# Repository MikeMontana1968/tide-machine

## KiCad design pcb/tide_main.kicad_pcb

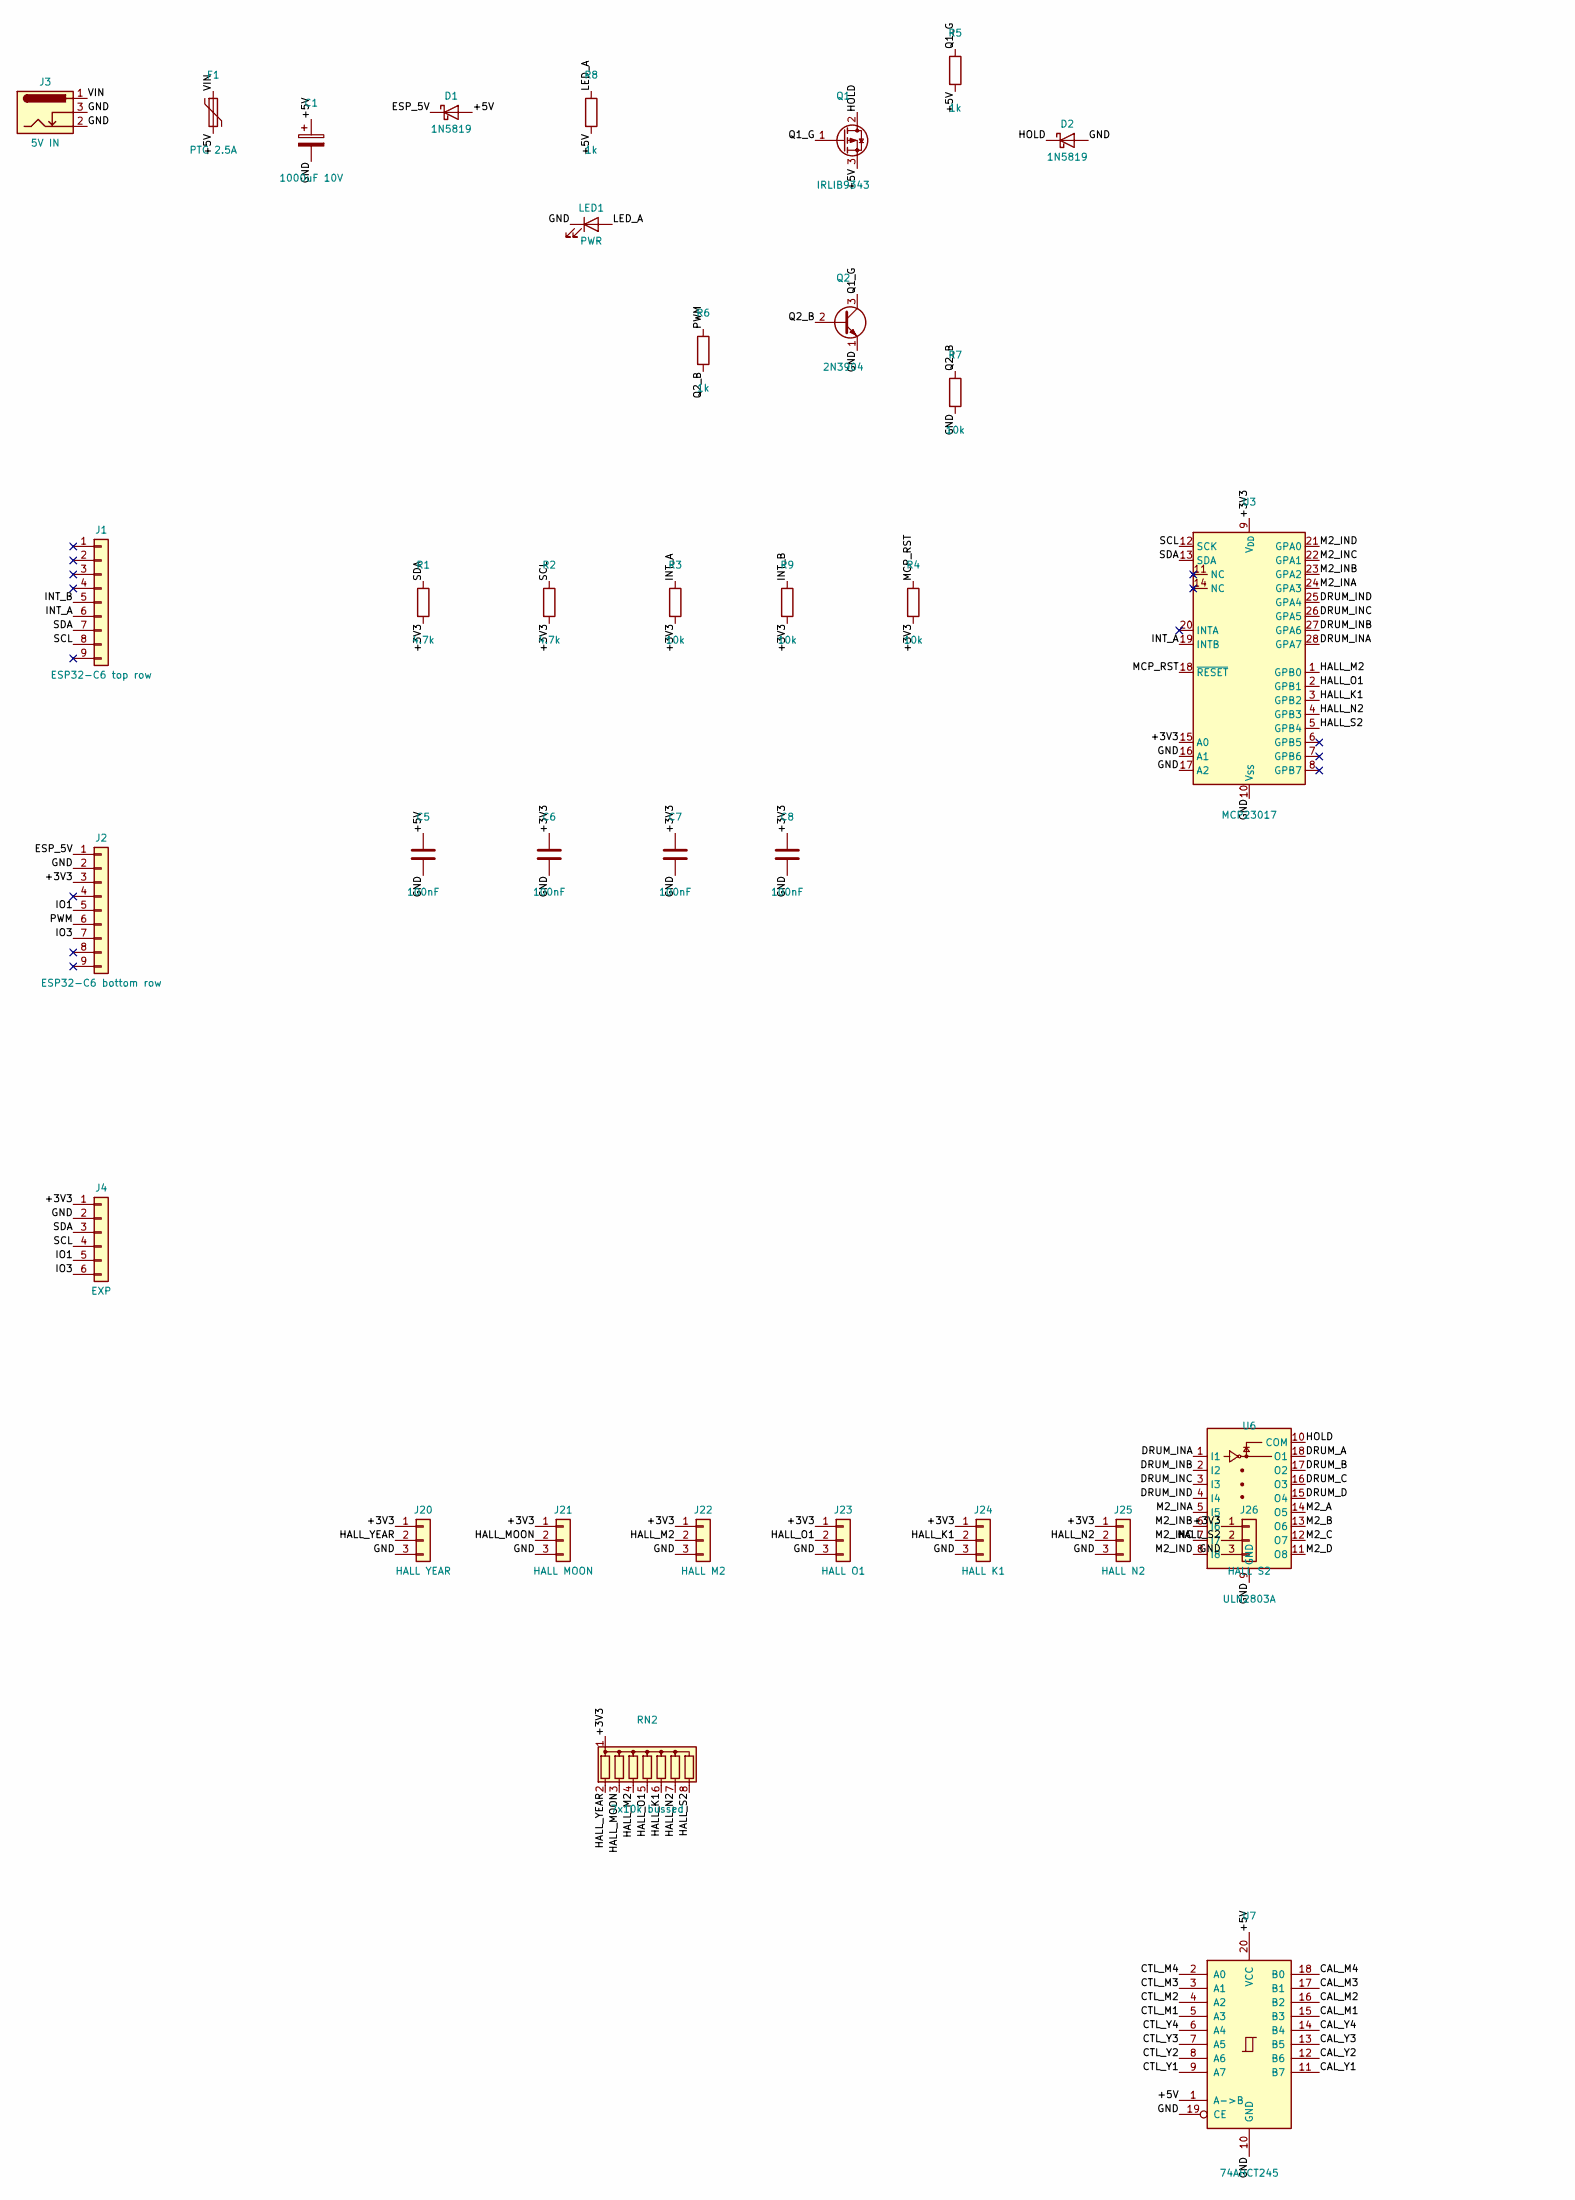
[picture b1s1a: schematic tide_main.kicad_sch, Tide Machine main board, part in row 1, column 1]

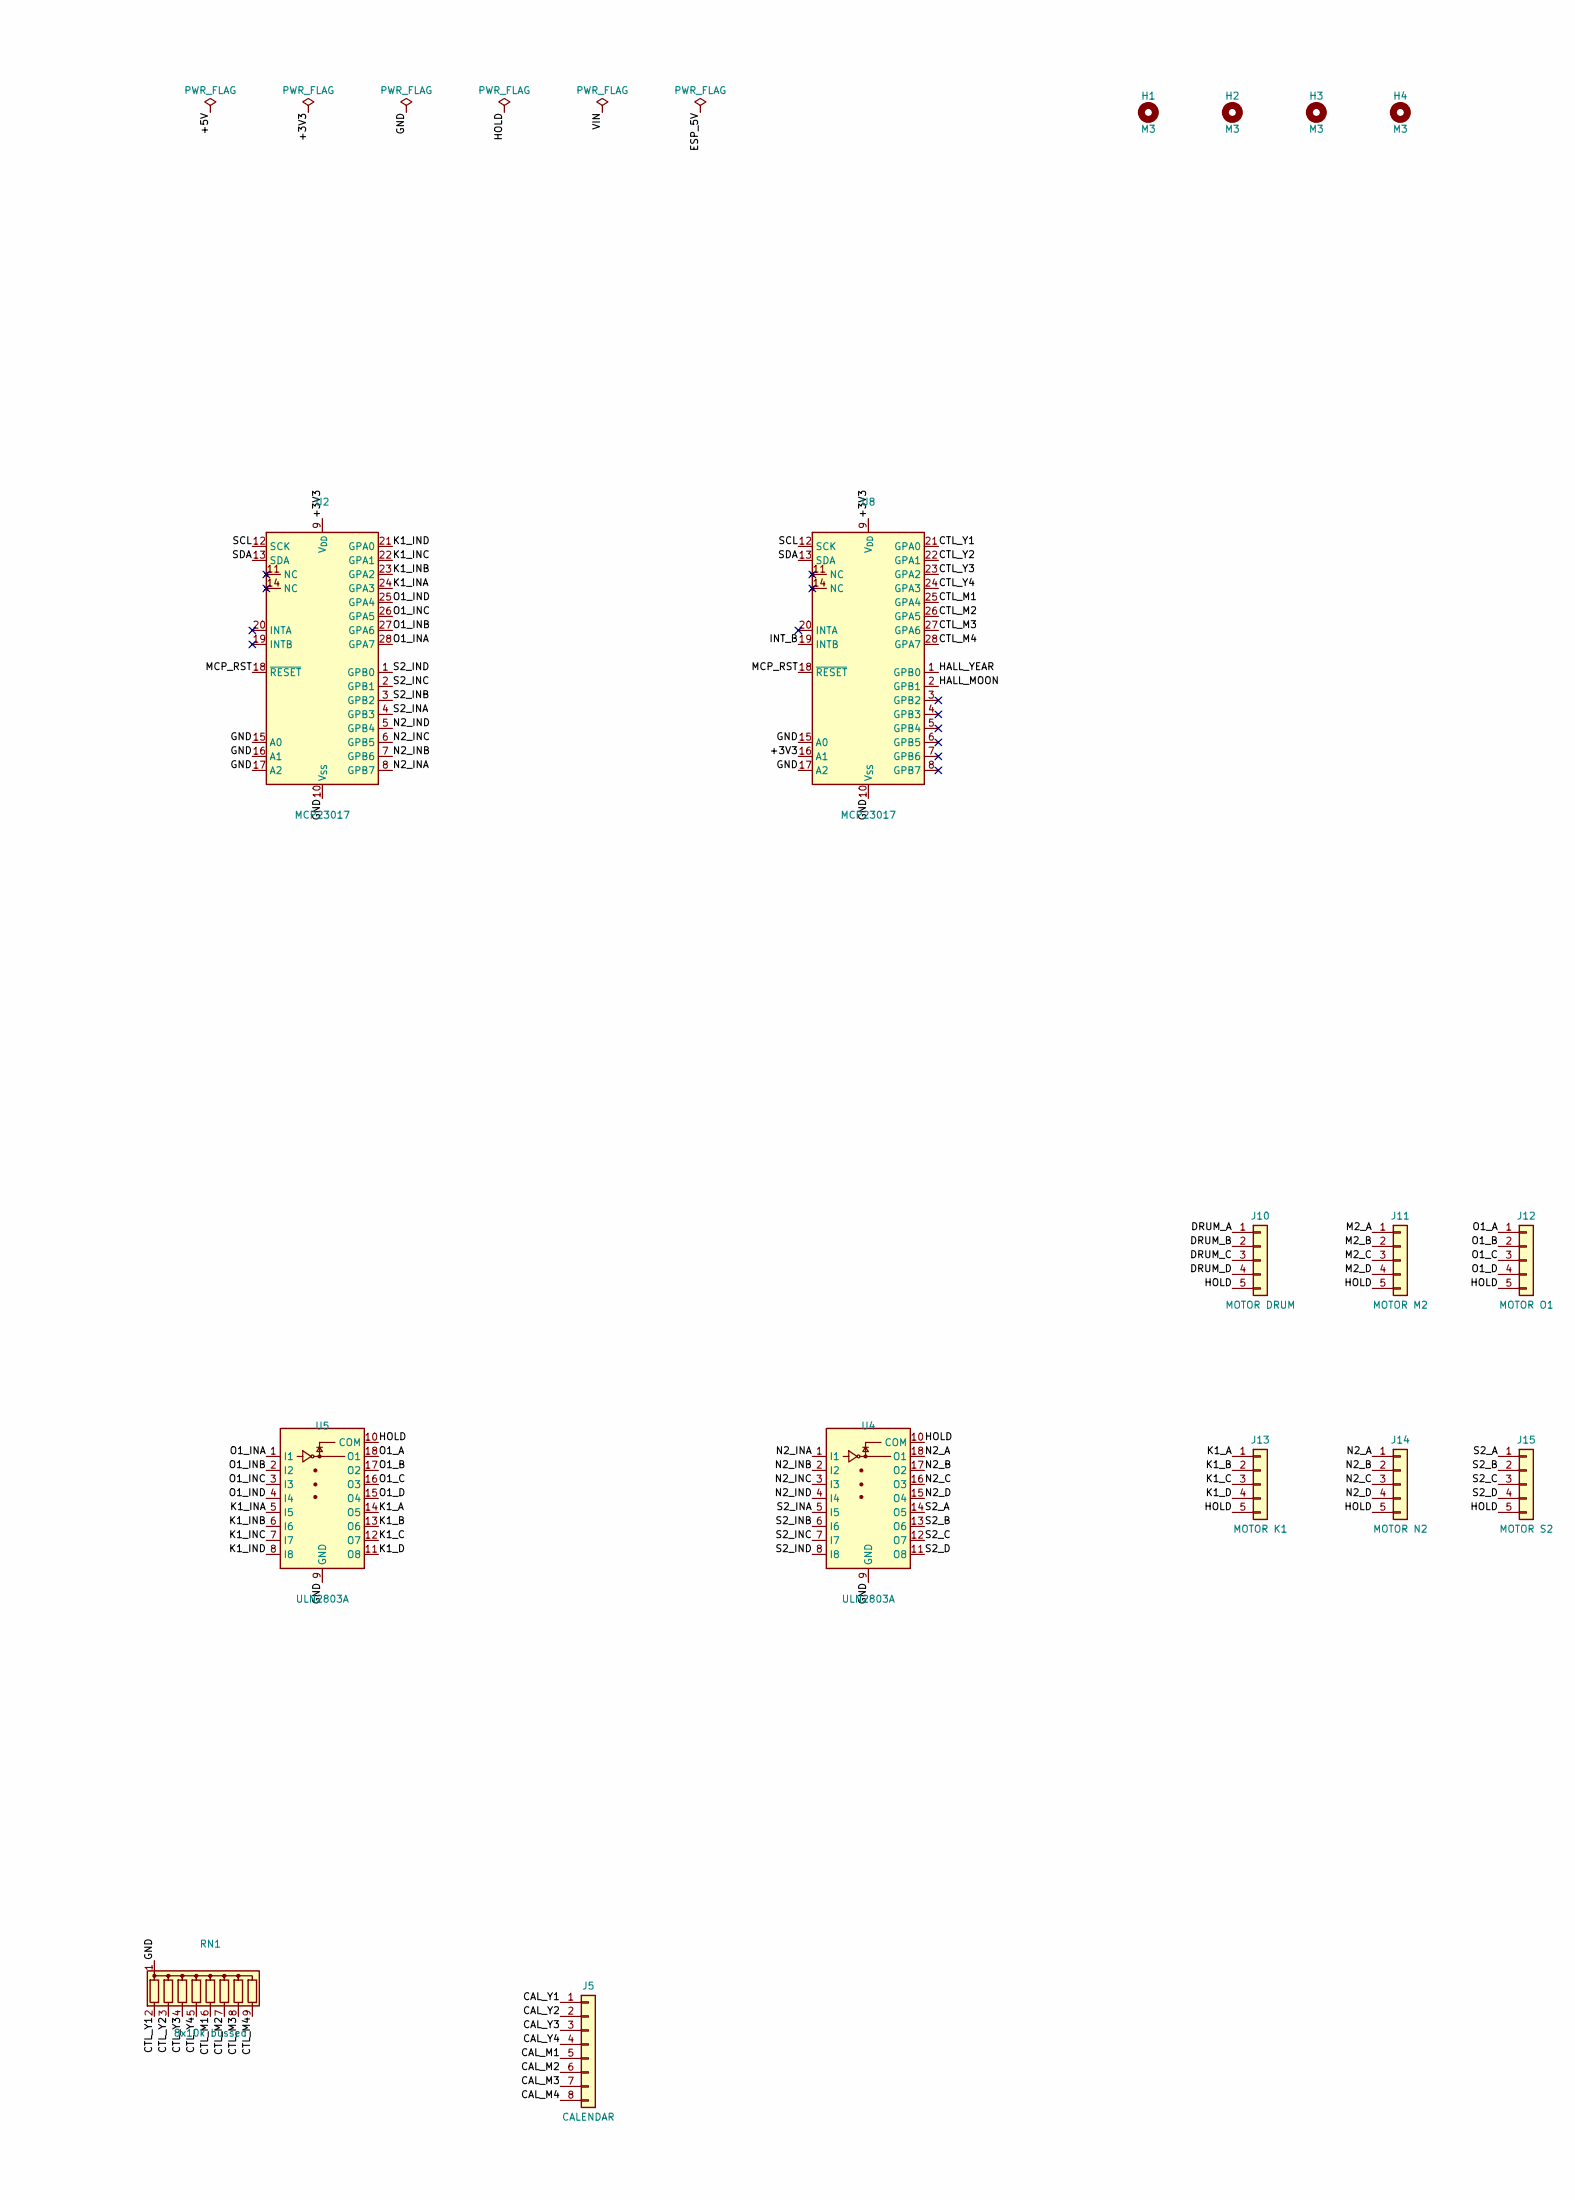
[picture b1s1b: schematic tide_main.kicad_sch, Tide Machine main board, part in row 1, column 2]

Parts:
C1: 1000uF 10V; CP_Radial_D10.0mm_P5.00mm
C5, C6, C7, C8: 100nF; C_Disc_D5.0mm_W2.5mm_P2.50mm
D1, D2: 1N5819; D_DO-41_SOD81_P10.16mm_Horizontal
F1: PTC 2.5A; Fuse_Bourns_MF-RG300
H1, H2, H3, H4: M3; MountingHole_3.2mm_M3
J1: ESP32-C6 top row; PinSocket_1x09_P2.54mm_Vertical
J2: ESP32-C6 bottom row; PinSocket_1x09_P2.54mm_Vertical
J3: 5V IN; BarrelJack_CUI_PJ-102AH_Horizontal
J4: EXP; PinHeader_1x06_P2.54mm_Vertical
J5: CALENDAR; JST_XH_B8B-XH-A_1x08_P2.50mm_Vertical
J10: MOTOR DRUM; JST_XH_B5B-XH-A_1x05_P2.50mm_Vertical
J11: MOTOR M2; JST_XH_B5B-XH-A_1x05_P2.50mm_Vertical
J12: MOTOR O1; JST_XH_B5B-XH-A_1x05_P2.50mm_Vertical
J13: MOTOR K1; JST_XH_B5B-XH-A_1x05_P2.50mm_Vertical
J14: MOTOR N2; JST_XH_B5B-XH-A_1x05_P2.50mm_Vertical
J15: MOTOR S2; JST_XH_B5B-XH-A_1x05_P2.50mm_Vertical
J20: HALL YEAR; JST_XH_B3B-XH-A_1x03_P2.50mm_Vertical
J21: HALL MOON; JST_XH_B3B-XH-A_1x03_P2.50mm_Vertical
J22: HALL M2; JST_XH_B3B-XH-A_1x03_P2.50mm_Vertical
J23: HALL O1; JST_XH_B3B-XH-A_1x03_P2.50mm_Vertical
J24: HALL K1; JST_XH_B3B-XH-A_1x03_P2.50mm_Vertical
J25: HALL N2; JST_XH_B3B-XH-A_1x03_P2.50mm_Vertical
J26: HALL S2; JST_XH_B3B-XH-A_1x03_P2.50mm_Vertical
LED1: PWR; LED_D3.0mm
Q1: IRLIB9343; TO-220-3_Vertical
Q2: 2N3904; TO-92_Inline_Wide
R1, R2: 4.7k; R_Axial_DIN0207_L6.3mm_D2.5mm_P2.54mm_Vertical
R3, R4, R7, R9: 10k; R_Axial_DIN0207_L6.3mm_D2.5mm_P2.54mm_Vertical
R5, R6, R8: 1k; R_Axial_DIN0207_L6.3mm_D2.5mm_P2.54mm_Vertical
RN1: 8x10k bussed; R_Array_SIP9
RN2: 7x10k bussed; R_Array_SIP8
U2, U3, U8: MCP23017; DIP-28_W7.62mm_Socket
U4, U5, U6: ULN2803A; DIP-18_W7.62mm_Socket
U7: 74AHCT245; DIP-20_W7.62mm_Socket

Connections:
+3V3: C6.1, C7.1, C8.1, J2.3, J4.1, J20.1, J21.1, J22.1, J23.1, J24.1, J25.1, J26.1, R1.2, R2.2, R3.2, R4.2, R9.2, RN2.1 (common), U2.9 (V_{DD}), U3.9 (V_{DD}), U3.15 (A0), U8.9 (V_{DD}), U8.16 (A1)
+5V: C1.1, C5.1, D1.2 (A), F1.2, Q1.3 (S), R5.2, R8.2, U7.1 (A->B), U7.20 (VCC)
CAL_M1: J5.5, U7.15 (B3)
CAL_M2: J5.6, U7.16 (B2)
CAL_M3: J5.7, U7.17 (B1)
CAL_M4: J5.8, U7.18 (B0)
CAL_Y1: J5.1, U7.11 (B7)
CAL_Y2: J5.2, U7.12 (B6)
CAL_Y3: J5.3, U7.13 (B5)
CAL_Y4: J5.4, U7.14 (B4)
CTL_M1: RN1.6 (R5), U7.5 (A3), U8.25 (GPA4)
CTL_M2: RN1.7 (R6), U7.4 (A2), U8.26 (GPA5)
CTL_M3: RN1.8 (R7), U7.3 (A1), U8.27 (GPA6)
CTL_M4: RN1.9 (R8), U7.2 (A0), U8.28 (GPA7)
CTL_Y1: RN1.2 (R1), U7.9 (A7), U8.21 (GPA0)
CTL_Y2: RN1.3 (R2), U7.8 (A6), U8.22 (GPA1)
CTL_Y3: RN1.4 (R3), U7.7 (A5), U8.23 (GPA2)
CTL_Y4: RN1.5 (R4), U7.6 (A4), U8.24 (GPA3)
DRUM_A: J10.1, U6.18 (O1)
DRUM_B: J10.2, U6.17 (O2)
DRUM_C: J10.3, U6.16 (O3)
DRUM_D: J10.4, U6.15 (O4)
DRUM_INA: U3.28 (GPA7), U6.1 (I1)
DRUM_INB: U3.27 (GPA6), U6.2 (I2)
DRUM_INC: U3.26 (GPA5), U6.3 (I3)
DRUM_IND: U3.25 (GPA4), U6.4 (I4)
ESP_5V: D1.1 (K), J2.1
GND: C1.2, C5.2, C6.2, C7.2, C8.2, D2.2 (A), J2.2, J3.2, J3.3, J4.2, J20.3, J21.3, J22.3, J23.3, J24.3, J25.3, J26.3, LED1.1 (K), Q2.1 (E), R7.2, RN1.1 (common), U2.10 (V_{SS}), U2.15 (A0), U2.16 (A1), U2.17 (A2), U3.10 (V_{SS}), U3.16 (A1), U3.17 (A2), U4.9 (GND), U5.9 (GND), U6.9 (GND), U7.10 (GND), U7.19 (CE), U8.10 (V_{SS}), U8.15 (A0), U8.17 (A2)
HALL_K1: J24.2, RN2.6 (R5), U3.3 (GPB2)
HALL_M2: J22.2, RN2.4 (R3), U3.1 (GPB0)
HALL_MOON: J21.2, RN2.3 (R2), U8.2 (GPB1)
HALL_N2: J25.2, RN2.7 (R6), U3.4 (GPB3)
HALL_O1: J23.2, RN2.5 (R4), U3.2 (GPB1)
HALL_S2: J26.2, RN2.8 (R7), U3.5 (GPB4)
HALL_YEAR: J20.2, RN2.2 (R1), U8.1 (GPB0)
HOLD: D2.1 (K), J10.5, J11.5, J12.5, J13.5, J14.5, J15.5, Q1.2 (D), U4.10 (COM), U5.10 (COM), U6.10 (COM)
INT_A: J1.6, R3.1, U3.19 (INTB)
INT_B: J1.5, R9.1, U8.19 (INTB)
IO1: J2.5, J4.5
IO3: J2.7, J4.6
K1_A: J13.1, U5.14 (O5)
K1_B: J13.2, U5.13 (O6)
K1_C: J13.3, U5.12 (O7)
K1_D: J13.4, U5.11 (O8)
K1_INA: U2.24 (GPA3), U5.5 (I5)
K1_INB: U2.23 (GPA2), U5.6 (I6)
K1_INC: U2.22 (GPA1), U5.7 (I7)
K1_IND: U2.21 (GPA0), U5.8 (I8)
LED_A: LED1.2 (A), R8.1
M2_A: J11.1, U6.14 (O5)
M2_B: J11.2, U6.13 (O6)
M2_C: J11.3, U6.12 (O7)
M2_D: J11.4, U6.11 (O8)
M2_INA: U3.24 (GPA3), U6.5 (I5)
M2_INB: U3.23 (GPA2), U6.6 (I6)
M2_INC: U3.22 (GPA1), U6.7 (I7)
M2_IND: U3.21 (GPA0), U6.8 (I8)
MCP_RST: R4.1, U2.18 (~RESET), U3.18 (~RESET), U8.18 (~RESET)
N2_A: J14.1, U4.18 (O1)
N2_B: J14.2, U4.17 (O2)
N2_C: J14.3, U4.16 (O3)
N2_D: J14.4, U4.15 (O4)
N2_INA: U2.8 (GPB7), U4.1 (I1)
N2_INB: U2.7 (GPB6), U4.2 (I2)
N2_INC: U2.6 (GPB5), U4.3 (I3)
N2_IND: U2.5 (GPB4), U4.4 (I4)
O1_A: J12.1, U5.18 (O1)
O1_B: J12.2, U5.17 (O2)
O1_C: J12.3, U5.16 (O3)
O1_D: J12.4, U5.15 (O4)
O1_INA: U2.28 (GPA7), U5.1 (I1)
O1_INB: U2.27 (GPA6), U5.2 (I2)
O1_INC: U2.26 (GPA5), U5.3 (I3)
O1_IND: U2.25 (GPA4), U5.4 (I4)
PWM: J2.6, R6.1
Q1_G: Q1.1 (G), Q2.3 (C), R5.1
Q2_B: Q2.2 (B), R6.2, R7.1
S2_A: J15.1, U4.14 (O5)
S2_B: J15.2, U4.13 (O6)
S2_C: J15.3, U4.12 (O7)
S2_D: J15.4, U4.11 (O8)
S2_INA: U2.4 (GPB3), U4.5 (I5)
S2_INB: U2.3 (GPB2), U4.6 (I6)
S2_INC: U2.2 (GPB1), U4.7 (I7)
S2_IND: U2.1 (GPB0), U4.8 (I8)
SCL: J1.8, J4.4, R2.1, U2.12 (SCK), U3.12 (SCK), U8.12 (SCK)
SDA: J1.7, J4.3, R1.1, U2.13 (SDA), U3.13 (SDA), U8.13 (SDA)
VIN: F1.1, J3.1

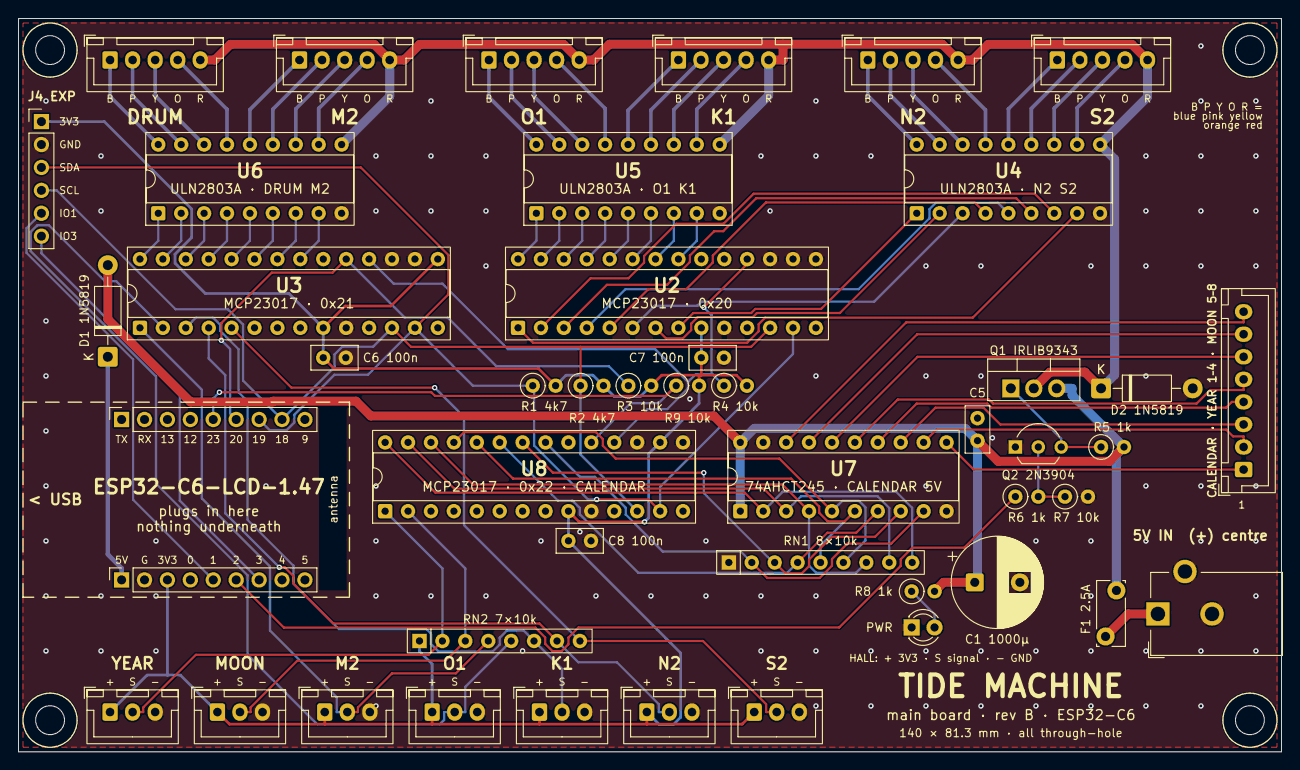
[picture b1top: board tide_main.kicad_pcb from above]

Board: 2 copper layers, 140.0 x 81.3 mm, 51 parts (0 on the bottom side), 88 nets.

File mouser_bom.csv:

Mouser Part Number,Manufacturer Part Number,Manufacturer,Quantity,Description,Customer Part Number,Notes
,SSW-109-01-T-S,Samtec,3,"Socket strip 1x9, 2.54 mm, through hole: the ESP32-C6 socket","J1, J2",Any 1x9 2.54 mm female header about 8.5 mm tall will do. (The Waveshare ESP32-C6-LCD-1.47 itself is bought separately.)
,MCP23017-E/SP,Microchip,4,"I/O expander, I2C, DIP-28 (0.3 in)","U2, U3, U8",
511-ULN2803A,ULN2803A,STMicroelectronics,4,"8x Darlington array, DIP-18","U4, U5, U6",
,SN74AHCT245N,Texas Instruments,2,"Octal buffer, TTL inputs, DIP-20",U7,
,110-43-328-41-001000,Mill-Max,3,"DIP socket 28-pin, 0.300 in rows","U2, U3, U8",0.3 in (skinny) -- not the 0.6 in 28-pin.
,110-43-318-41-001000,Mill-Max,3,"DIP socket 18-pin, 0.300 in",U4-U6,
,110-43-320-41-001000,Mill-Max,1,"DIP socket 20-pin, 0.300 in",U7,
,IRLIB9343PBF,Infineon,2,"P-channel MOSFET, logic level, -55 V, TO-220 FullPAK",Q1,
,2N3904BU,onsemi,5,"NPN transistor, TO-92",Q2,
,1N5819G,onsemi,5,"Schottky diode 1 A 40 V, DO-41","D1, D2",
,MF-R250,Bourns,2,"PTC resettable fuse 2.5 A hold, radial, 5.1 mm leads",F1,
,EEU-FR1C102,Panasonic,2,"Electrolytic 1000 uF 16 V, 10 x 16 mm, 5 mm pitch",C1,
,C320C104K5R5TA,KEMET,25,"Ceramic 100 nF 50 V X7R, radial, 2.54 mm leads",C5-C8 + Hall carriers,
,MFR-25FBF52-1K,YAGEO,10,Resistor 1 k 1/4 W 1% metal film,"R5, R6, R8",
,MFR-25FBF52-10K,YAGEO,10,Resistor 10 k 1/4 W 1% metal film,"R3, R4, R7, R9",
,MFR-25FBF52-4K7,YAGEO,10,Resistor 4.7 k 1/4 W 1% metal film,"R1, R2",
,4608X-101-103LF,Bourns,2,"Resistor network 7x 10 k bussed, SIP-8",RN2,
,4609X-101-103LF,Bourns,2,"Resistor network 8x 10 k bussed, SIP-9",RN1,
604-WP710A10GD,WP710A10GD,Kingbright,2,LED 3 mm green,LED1,
490-PJ-102AH,PJ-102AH,Same Sky,2,"DC jack 5.5 mm, 2.0 mm pin, through hole",J3,2.0 mm pin is the standard mate for a '5.5 x 2.1' plug. Don't use a 2.5 mm plug.
,B5B-XH-A(LF)(SN),JST,7,"XH header 5-pin, top entry",J10-J15,The 28BYJ-48's own plug fits.
,B3B-XH-A(LF)(SN),JST,8,"XH header 3-pin, top entry",J20-J26,
,B8B-XH-A(LF)(SN),JST,2,"XH header 8-pin, top entry",J5,
,XHP-3,JST,10,XH housing 3-pin,Hall cables,
,XHP-8,JST,2,XH housing 8-pin,Calendar cable,
,SXH-001T-P0.6,JST,50,"XH crimp contact, 22-28 AWG",Hall + calendar cables,Crimp with a generic JST-XH crimper.
,61300611121,Wurth Elektronik,2,"Pin header 1x6, 2.54 mm",J4,
,DRV5013AGQLPG,Texas Instruments,8,"Hall latch +/-6 mT, TO-92 (LPG)",Hall carriers,Bench-test beside a running 28BYJ-48 before building seven carriers.
,DRV5013BCQLPG,Texas Instruments,3,"Hall latch +/-12 mT, TO-92 (LPG)",(bench test),"The less sensitive variant, in case motor stray fields trip the AG."
,GST18U05-P1J,MEAN WELL,1,"5 V 3 A wall adapter, 5.5 x 2.1 mm plug, centre positive",(power),The SGA18U05-P1J is being discontinued. Any 5 V 3 A centre-positive 5.5 x 2.1 adapter will do.

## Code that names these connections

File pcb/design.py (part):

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MOTORS = ["DRUM", "M2", "O1", "K1", "N2", "S2"]          # left to right on the board = machine +x to -x as seen
                                                         # from behind, so each cable runs straight to its motor
HALLS = ["YEAR", "MOON", "M2", "O1", "K1", "N2", "S2"]   # bottom edge, left to right
COIL = "ABCD"                                            # A blue, B pink, C yellow, D orange; red = HOLD

# MCP23017 port bit -> motor wire, ordered so the traces don't cross. Firmware reads this table.
#   U3 (0x21) GPA drives ULN U6 (DRUM, M2);  U2 (0x20) GPA drives U5 (O1, K1), GPB drives U4 (N2, S2)
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CAL_HALL_BITS = {"YEAR": 0, "MOON": 1}                              # U8 GPB0-1

# ESP32-C6 GPIO use (the rest of the header pins stay unconnected)
ESP_GPIO = {18: "SCL", 19: "SDA", 20: "INT_A", 23: "INT_B", 2: "PWM", 1: "IO1", 3: "IO3"}

def mcp_pin(port, bit):
    return (21 + bit) if port == "GPA" else (1 + bit)
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def esp_pads(row):
    out = {}
    for k, name in enumerate(row):
        n = {"5V": "ESP_5V", "GND": "GND", "3V3": "+3V3"}.get(name) if isinstance(name, str) else ESP_GPIO.get(name)
        if n:
            out[k + 1] = n
    return out
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MPITCH = 21.0
for i, m in enumerate(MOTORS):
    part(f"J{10 + i}", "XH5", f"MOTOR {m}", "JST B5B-XH-A", 10.15 + MPITCH * i, 4.6, 0,
         {1: f"{m}_A", 2: f"{m}_B", 3: f"{m}_C", 4: f"{m}_D", 5: "HOLD"}, "28BYJ-48 plug: blue pink yellow orange red")

# ---- ULN2803A (DIP-18): inputs 1-8 (1B-8B), 9 GND, 10 COM, outputs 18..11 (1C..8C); centred under their socket pairs
for u, x in (("U6", 15.494), ("U5", 57.404), ("U4", 99.568)):
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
